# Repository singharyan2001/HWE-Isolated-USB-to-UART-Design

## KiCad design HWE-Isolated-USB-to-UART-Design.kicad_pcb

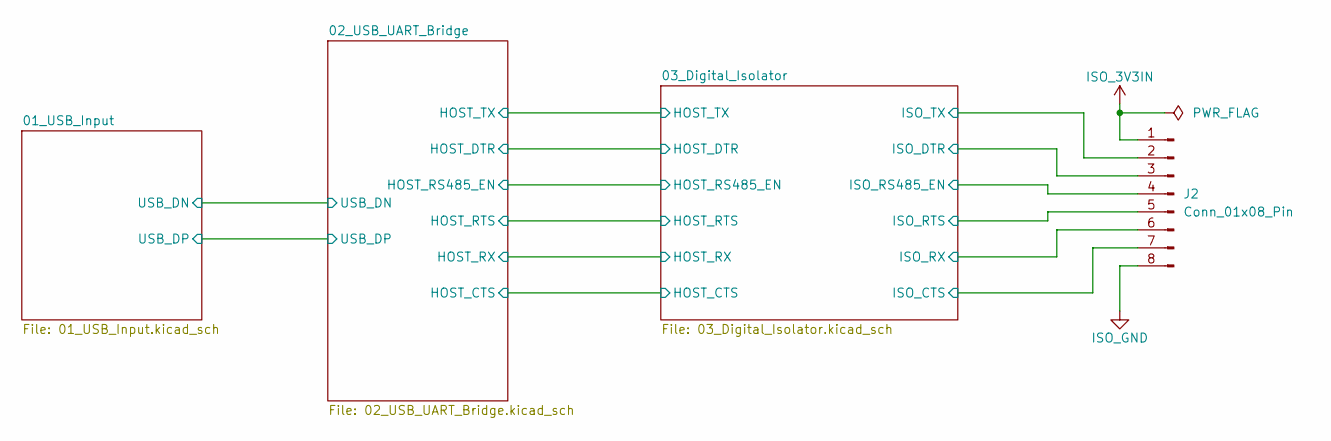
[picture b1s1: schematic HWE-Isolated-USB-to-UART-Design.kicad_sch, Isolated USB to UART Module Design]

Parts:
J2: Conn_01x08_Pin; PinHeader_1x08_P2.54mm_Horizontal

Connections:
/03_Digital_Isolator/ISO_CTS: J2.7; also elsewhere on the board
/03_Digital_Isolator/ISO_DTR: J2.3; also elsewhere on the board
/03_Digital_Isolator/ISO_RS485_EN: J2.4; also elsewhere on the board
/03_Digital_Isolator/ISO_RTS: J2.5; also elsewhere on the board
/03_Digital_Isolator/ISO_RX: J2.6; also elsewhere on the board
/03_Digital_Isolator/ISO_TX: J2.2; also elsewhere on the board
ISO_3V3IN: J2.1
ISO_GND: J2.8; also elsewhere on the board

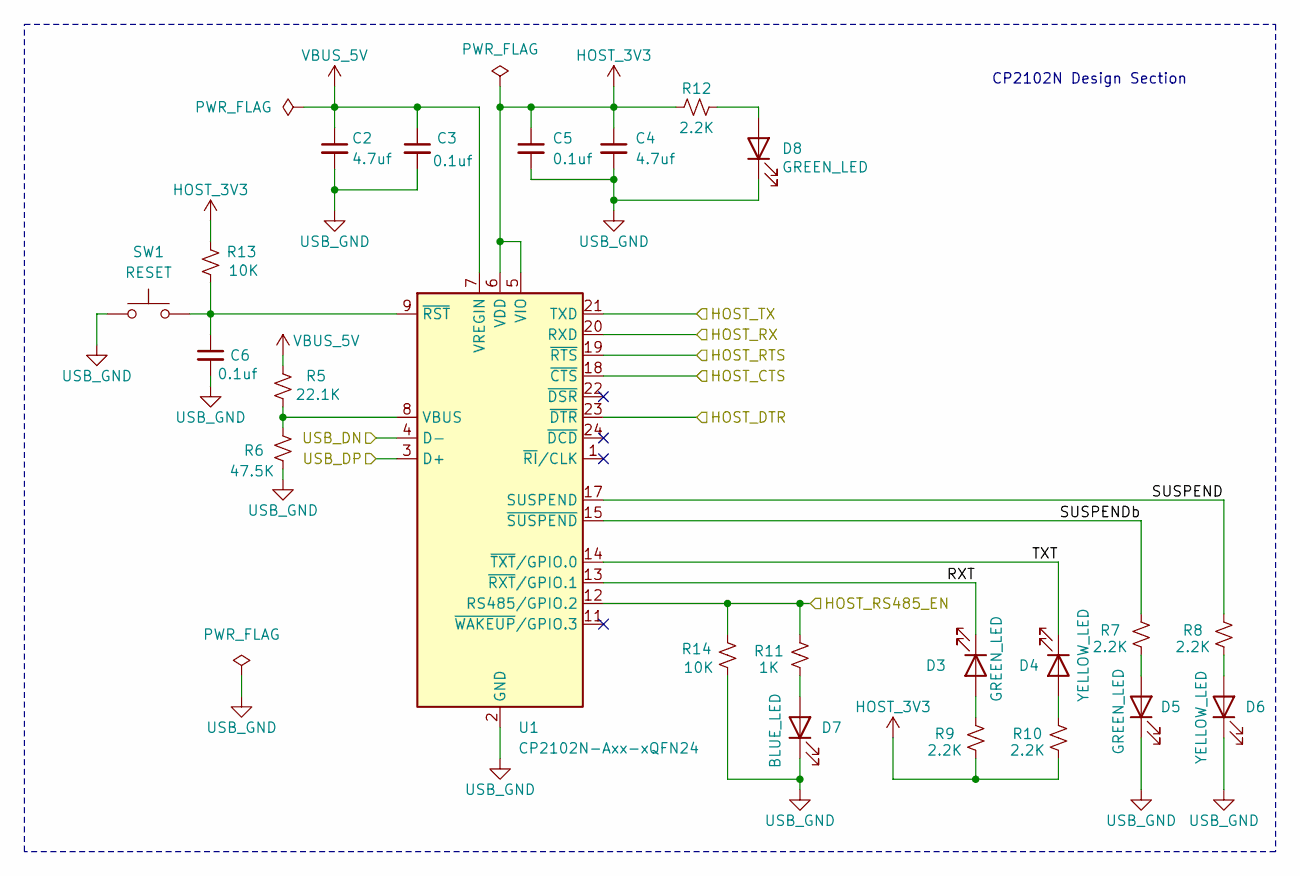
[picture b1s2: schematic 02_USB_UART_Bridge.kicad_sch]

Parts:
C2, C4: 4.7uf; C_0805_2012Metric_Pad1.18x1.45mm_HandSolder
C3, C5, C6: 0.1uf; C_0805_2012Metric_Pad1.18x1.45mm_HandSolder
D3, D5, D8: GREEN_LED; LED_0805_2012Metric_Pad1.15x1.40mm_HandSolder
D4, D6: YELLOW_LED; LED_0805_2012Metric_Pad1.15x1.40mm_HandSolder
D7: BLUE_LED; LED_0805_2012Metric_Pad1.15x1.40mm_HandSolder
R5: 22.1K; R_0805_2012Metric_Pad1.20x1.40mm_HandSolder
R6: 47.5K; R_0805_2012Metric_Pad1.20x1.40mm_HandSolder
R7, R8, R9, R10, R12: 2.2K; R_0805_2012Metric_Pad1.20x1.40mm_HandSolder
R11: 1K; R_0805_2012Metric_Pad1.20x1.40mm_HandSolder
R13, R14: 10K; R_0805_2012Metric_Pad1.20x1.40mm_HandSolder
SW1: RESET; SW_SPST_CK_RS282G05A3
U1: CP2102N-Axx-xQFN24; QFN-24-1EP_4x4mm_P0.5mm_EP2.6x2.6mm_ThermalVias

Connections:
/01_USB_Input/USB_DN: U1.4 (D-); also elsewhere on the board
/01_USB_Input/USB_DP: U1.3 (D+); also elsewhere on the board
/02_USB_UART_Bridge/HOST_CTS: U1.18 (~CTS); also elsewhere on the board
/02_USB_UART_Bridge/HOST_DTR: U1.23 (~DTR); also elsewhere on the board
/02_USB_UART_Bridge/HOST_RS485_EN: R11.1, R14.2, U1.12 (RS485/GPIO.2); also elsewhere on the board
/02_USB_UART_Bridge/HOST_RTS: U1.19 (~RTS); also elsewhere on the board
/02_USB_UART_Bridge/HOST_RX: U1.20 (RXD); also elsewhere on the board
/02_USB_UART_Bridge/HOST_TX: U1.21 (TXD); also elsewhere on the board
/02_USB_UART_Bridge/RXT: D3.1 (K), U1.13 (~RXT/GPIO.1)
/02_USB_UART_Bridge/SUSPEND: R8.1, U1.17 (SUSPEND)
/02_USB_UART_Bridge/SUSPENDb: R7.1, U1.15 (~SUSPEND)
/02_USB_UART_Bridge/TXT: D4.1 (K), U1.14 (~TXT/GPIO.0)
HOST_3V3: C4.1, C5.1, R9.2, R10.2, R12.1, R13.1, U1.5 (VIO), U1.6 (VDD); also elsewhere on the board
unnamed: D3.2 (A), R9.1
unnamed: D4.2 (A), R10.1
unnamed: D5.2 (A), R7.2
unnamed: D6.2 (A), R8.2
unnamed: D7.2 (A), R11.2
unnamed: D8.2 (A), R12.2
unnamed: R5.2, R6.1, U1.8 (VBUS)
unnamed: C6.1, R13.2, SW1.2, U1.9 (~RST)
USB_GND: C2.2, C3.2, C4.2, C5.2, C6.2, D5.1 (K), D6.1 (K), D7.1 (K), D8.1 (K), R6.2, R14.1, SW1.1, U1.2 (GND), U1.25 (GND); also elsewhere on the board
VBUS_5V: C2.1, C3.1, R5.1, U1.7 (VREGIN); also elsewhere on the board

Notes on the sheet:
CP2102N Design Section

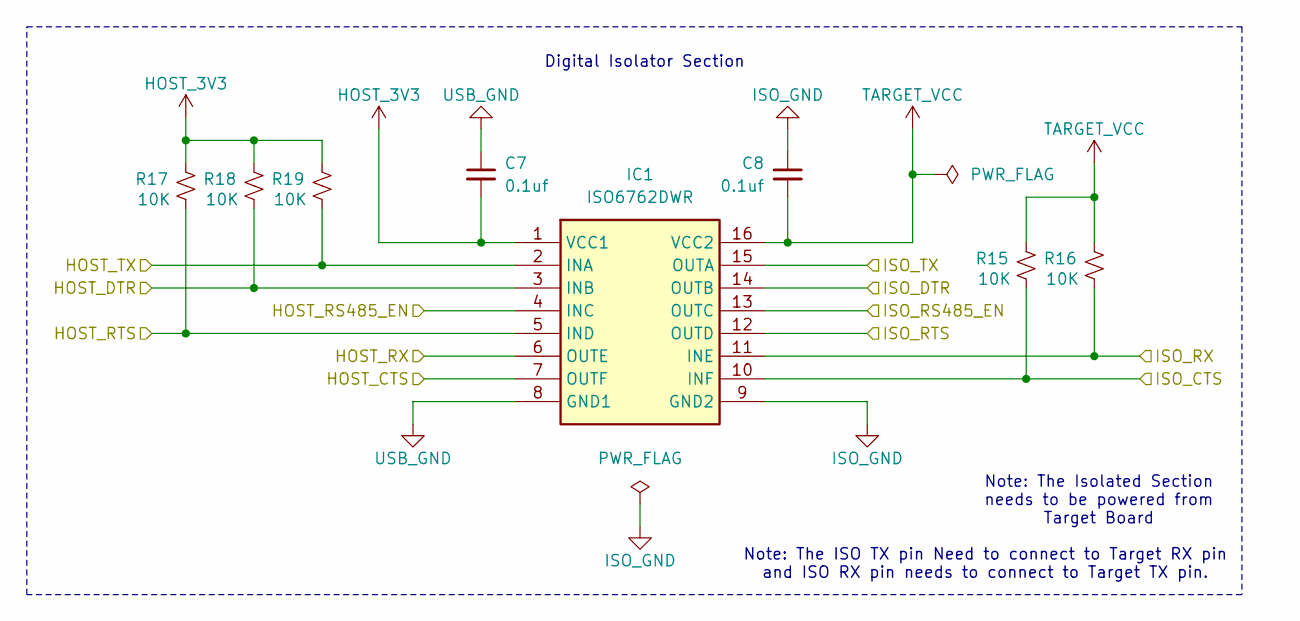
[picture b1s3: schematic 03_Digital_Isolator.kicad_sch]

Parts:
C7, C8: 0.1uf; C_0805_2012Metric_Pad1.18x1.45mm_HandSolder
IC1: ISO6762DWR; SOIC127P1030X265-16N; Mouser Part Number 595-ISO6762DWR
R15, R16, R17, R18, R19: 10K; R_0805_2012Metric_Pad1.20x1.40mm_HandSolder

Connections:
/02_USB_UART_Bridge/HOST_CTS: IC1.7 (OUTF); also elsewhere on the board
/02_USB_UART_Bridge/HOST_DTR: IC1.3 (INB), R18.1; also elsewhere on the board
/02_USB_UART_Bridge/HOST_RS485_EN: IC1.4 (INC); also elsewhere on the board
/02_USB_UART_Bridge/HOST_RTS: IC1.5 (IND), R17.1; also elsewhere on the board
/02_USB_UART_Bridge/HOST_RX: IC1.6 (OUTE); also elsewhere on the board
/02_USB_UART_Bridge/HOST_TX: IC1.2 (INA), R19.1; also elsewhere on the board
/03_Digital_Isolator/ISO_CTS: IC1.10 (INF), R15.1; also elsewhere on the board
/03_Digital_Isolator/ISO_DTR: IC1.14 (OUTB); also elsewhere on the board
/03_Digital_Isolator/ISO_RS485_EN: IC1.13 (OUTC); also elsewhere on the board
/03_Digital_Isolator/ISO_RTS: IC1.12 (OUTD); also elsewhere on the board
/03_Digital_Isolator/ISO_RX: IC1.11 (INE), R16.1; also elsewhere on the board
/03_Digital_Isolator/ISO_TX: IC1.15 (OUTA); also elsewhere on the board
HOST_3V3: C7.2, IC1.1 (VCC1), R17.2, R18.2, R19.2; also elsewhere on the board
ISO_GND: C8.1, IC1.9 (GND2); also elsewhere on the board
TARGET_VCC: C8.2, IC1.16 (VCC2), R15.2, R16.2
USB_GND: C7.1, IC1.8 (GND1); also elsewhere on the board

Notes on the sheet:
Note: The ISO TX pin Need to connect to Target RX pin and ISO RX pin needs to connect to Target TX pin.
Note: The Isolated Section needs to be powered from Target Board
Digital Isolator Section

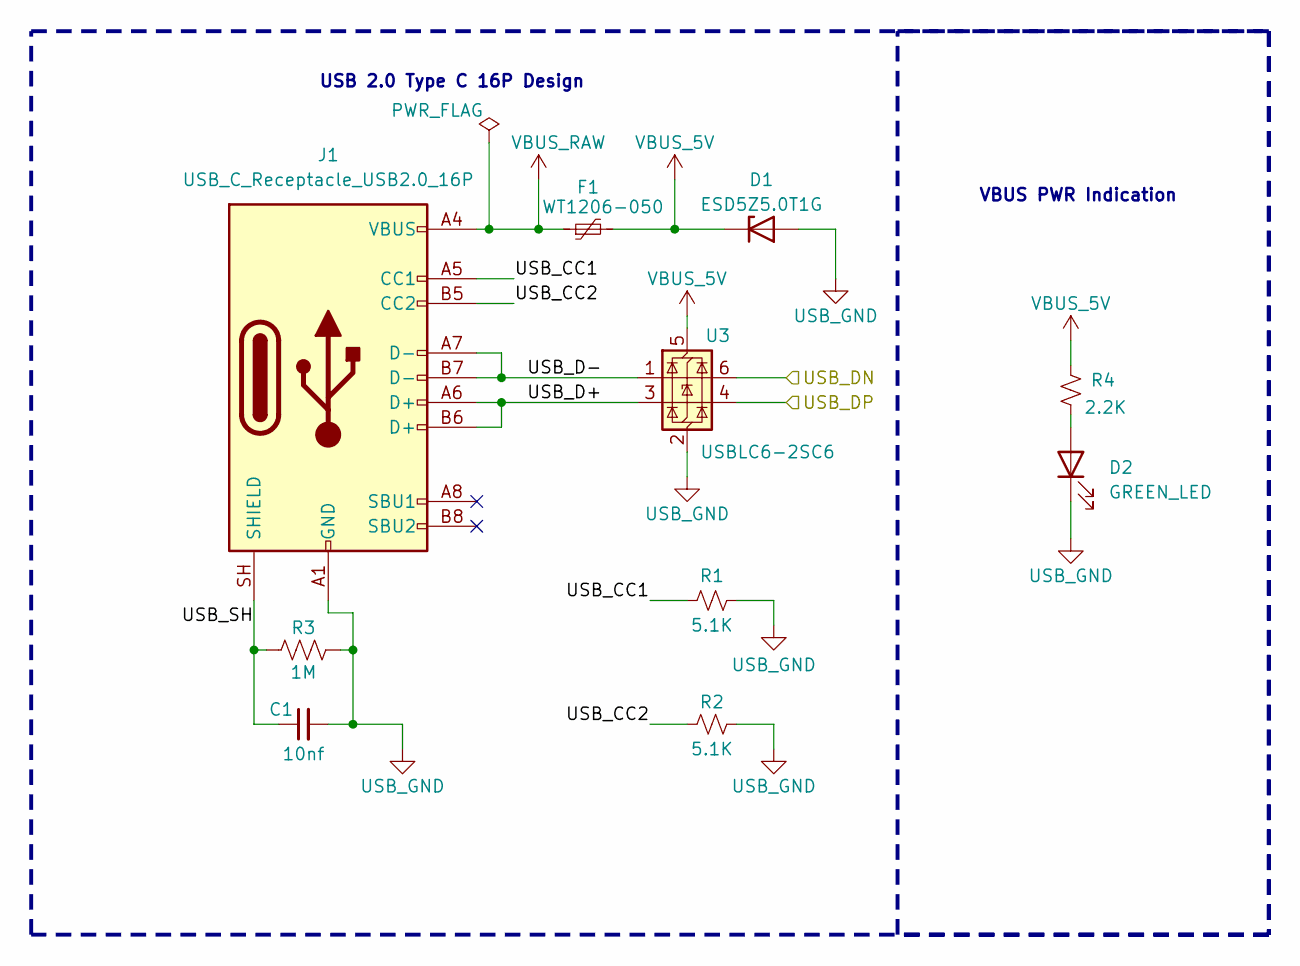
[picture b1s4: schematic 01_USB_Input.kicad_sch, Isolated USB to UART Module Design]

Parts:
C1: 10nf; C_0805_2012Metric_Pad1.18x1.45mm_HandSolder
D1: ESD5Z5.0T1G; D_SOD-523
D2: GREEN_LED; LED_0805_2012Metric_Pad1.15x1.40mm_HandSolder
F1: WT1206-050; Fuse_1206_3216Metric_Pad1.42x1.75mm_HandSolder
J1: USB_C_Receptacle_USB2.0_16P; USB_C_Receptacle_HRO_TYPE-C-31-M-12
R1, R2: 5.1K; R_0805_2012Metric_Pad1.20x1.40mm_HandSolder
R3: 1M; R_1206_3216Metric_Pad1.30x1.75mm_HandSolder
R4: 2.2K; R_0805_2012Metric_Pad1.20x1.40mm_HandSolder
U3: USBLC6-2SC6; SOT-23-6_Handsoldering

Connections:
/01_USB_Input/USB_CC1: J1.A5 (CC1), R1.2
/01_USB_Input/USB_CC2: J1.B5 (CC2), R2.2
/01_USB_Input/USB_D+: J1.A6 (D+), J1.B6 (D+), U3.3 (I/O2)
/01_USB_Input/USB_D-: J1.A7 (D-), J1.B7 (D-), U3.1 (I/O1)
/01_USB_Input/USB_DN: U3.6 (I/O1); also elsewhere on the board
/01_USB_Input/USB_DP: U3.4 (I/O2); also elsewhere on the board
/01_USB_Input/USB_SH: C1.1, J1.SH (SHIELD), R3.2
unnamed: D2.2 (A), R4.1
USB_GND: C1.2, D1.2 (A), D2.1 (K), J1.A1 (GND), J1.A12 (GND), J1.B1 (GND), J1.B12 (GND), R1.1, R2.1, R3.1, U3.2 (GND); also elsewhere on the board
VBUS_5V: D1.1 (K), F1.2, R4.2, U3.5 (VBUS); also elsewhere on the board
VBUS_RAW: F1.1, J1.A4 (VBUS), J1.A9 (VBUS), J1.B4 (VBUS), J1.B9 (VBUS)

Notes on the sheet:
USB 2.0 Type C 16P Design
VBUS PWR Indication

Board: 2 copper layers, 42 parts (0 on the bottom side), 38 nets, no tracks yet.
